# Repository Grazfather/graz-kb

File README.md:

# Graziano's keyboard

[ZMK configuration and keymap](https://github.com/Grazfather/zmk-config-grazkb)

* 58 key ergonomic wires keyboard.
* Full number row and alphabet (bare minimum for me)
* Low-profile choc switches
* 5 keys in the thumb cluster/row
* Designed using [Ergogen](https://github.com/ergogen/ergogen) and KiCad.
* ZMK Used for firmware.

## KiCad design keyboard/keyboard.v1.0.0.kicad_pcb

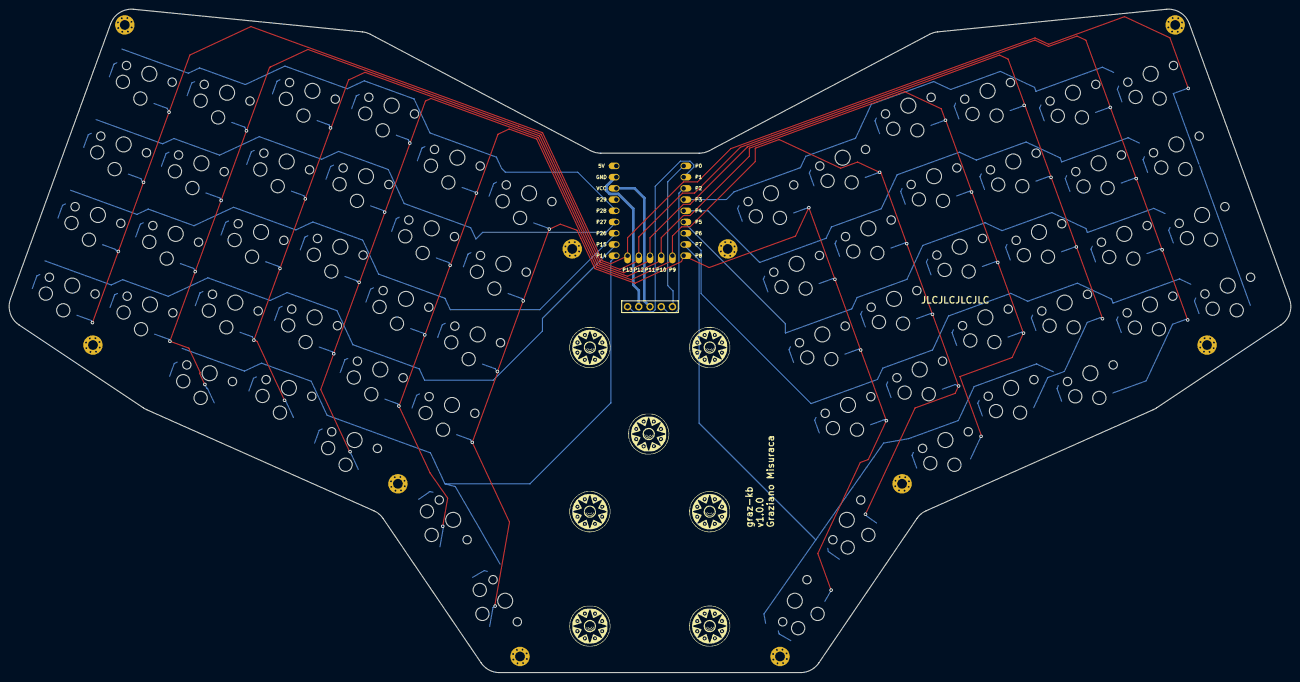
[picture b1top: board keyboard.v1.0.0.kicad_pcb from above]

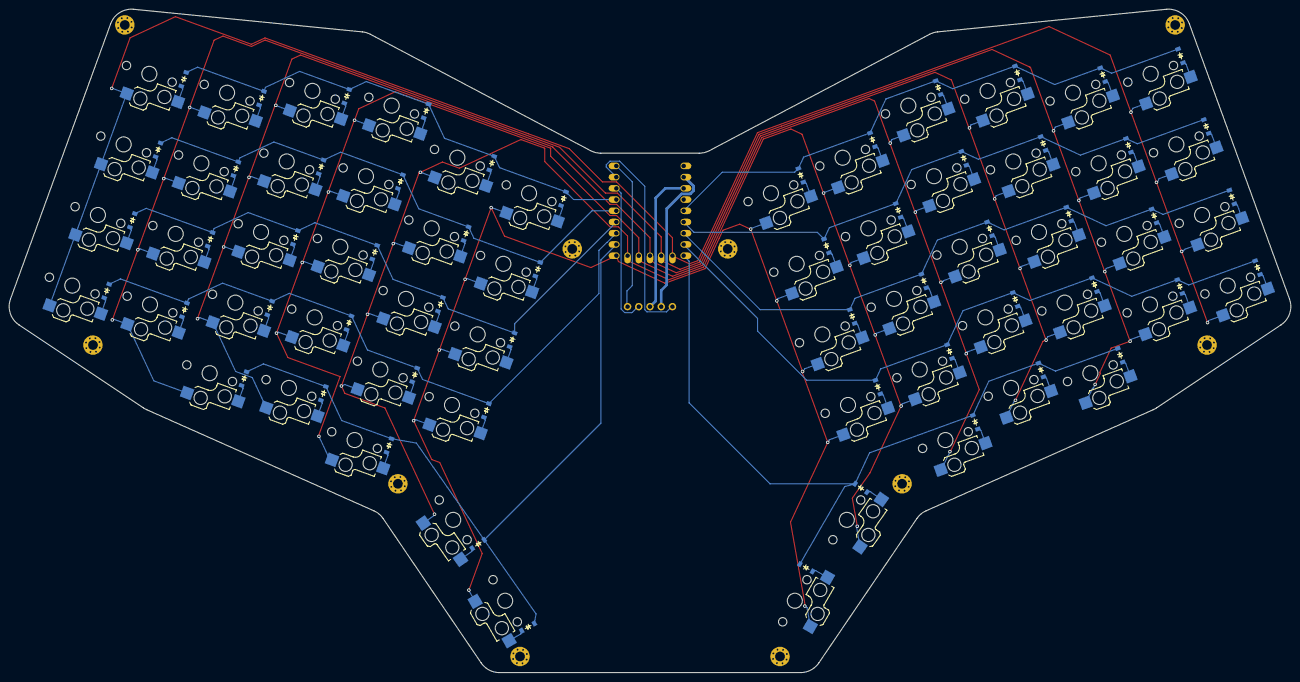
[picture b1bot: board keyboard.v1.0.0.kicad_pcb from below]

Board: 2 copper layers, 290.1 x 150.1 mm, 128 parts (116 on the bottom side), 79 nets.

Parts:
D1, D2, D3, D4, D5, D6, D7, D8, D9, D10, D11, D12, D13, D14, D15, D16, D17, D18, D19, D20, D21, D22, D23, D24, D25, D26, D27, D28, D29, D30, D31, D32, D33, D34, D35, D36, D37, D38, D39, D40, D41, D42, D43, D44, D45, D46, D47, D48, D49, D50, D51, D52, D53, D54, D55, D56, D57, D58: diode_tht_sod123
DISP1: nice_view
MCU1: Waveshare RP2040 Zero
S1, S2, S3, S4, S5, S6, S7, S8, S9, S10, S11, S12, S13, S14, S15, S16, S17, S18, S19, S20, S21, S22, S23, S24, S25, S26, S27, S28, S29, S30, S31, S32, S33, S34, S35, S36, S37, S38, S39, S40, S41, S42, S43, S44, S45, S46, S47, S48, S49, S50, S51, S52, S53, S54, S55, S56, S57, S58: switch_choc_v1_v2
_1, _2, _3, _3#2, _3#3, _4, _5, _6, _7, _8: MountingHole_2.2mm_M2_Pad_Via

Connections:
GND: DISP1.2, MCU1.22
OLED_MOSI: DISP1.5, MCU1.1
OLED_SCK: DISP1.4, MCU1.3
OLED_SS: DISP1.1, MCU1.2
VCC: DISP1.3, MCU1.21
col_index: MCU1.10, S20.1, S21.1, S22.1, S23.1, S28.1, S49.1, S50.1, S51.1, S52.1, S57.1
col_inner: MCU1.9, S24.1, S25.1, S26.1, S27.1, S29.1, S53.1, S54.1, S55.1, S56.1, S58.1
col_middle: MCU1.11, S15.1, S16.1, S17.1, S18.1, S19.1, S44.1, S45.1, S46.1, S47.1, S48.1
col_outer: MCU1.14, S1.1, S2.1, S3.1, S4.1, S30.1, S31.1, S32.1, S33.1
col_pinky: MCU1.13, S5.1, S6.1, S7.1, S8.1, S9.1, S34.1, S35.1, S36.1, S37.1, S38.1
col_ring: MCU1.12, S10.1, S11.1, S12.1, S13.1, S14.1, S39.1, S40.1, S41.1, S42.1, S43.1
far_thumb: D29.2, S29.2
home_thumb: D28.2, S28.2
index_bottom: D20.2, S20.2
index_home: D21.2, S21.2
index_mod: D19.2, S19.2
index_num: D23.2, S23.2
index_top: D22.2, S22.2
inner_bottom: D24.2, S24.2
inner_home: D25.2, S25.2
inner_num: D27.2, S27.2
inner_top: D26.2, S26.2
middle_bottom: D15.2, S15.2
middle_home: D16.2, S16.2
middle_mod: D14.2, S14.2
middle_num: D18.2, S18.2
middle_top: D17.2, S17.2
mirror_far_thumb: D58.2, S58.2
mirror_home_thumb: D57.2, S57.2
mirror_index_bottom: D49.2, S49.2
mirror_index_home: D50.2, S50.2
mirror_index_mod: D48.2, S48.2
mirror_index_num: D52.2, S52.2
mirror_index_top: D51.2, S51.2
mirror_inner_bottom: D53.2, S53.2
mirror_inner_home: D54.2, S54.2
mirror_inner_num: D56.2, S56.2
mirror_inner_top: D55.2, S55.2
mirror_middle_bottom: D44.2, S44.2
mirror_middle_home: D45.2, S45.2
mirror_middle_mod: D43.2, S43.2
mirror_middle_num: D47.2, S47.2
mirror_middle_top: D46.2, S46.2
mirror_outer_bottom: D30.2, S30.2
mirror_outer_home: D31.2, S31.2
mirror_outer_num: D33.2, S33.2
mirror_outer_top: D32.2, S32.2
mirror_pinky_bottom: D34.2, S34.2
mirror_pinky_home: D35.2, S35.2
mirror_pinky_num: D37.2, S37.2
mirror_pinky_top: D36.2, S36.2
mirror_ring_bottom: D39.2, S39.2
mirror_ring_home: D40.2, S40.2
mirror_ring_mod: D38.2, S38.2
mirror_ring_num: D42.2, S42.2
mirror_ring_top: D41.2, S41.2
mirror_row_bottom: D30.1, D34.1, D39.1, D44.1, D49.1, D53.1, MCU1.7
mirror_row_home: D31.1, D35.1, D40.1, D45.1, D50.1, D54.1, MCU1.6
mirror_row_mod: D38.1, D43.1, D48.1, D57.1, D58.1, MCU1.8
mirror_row_num: D33.1, D37.1, D42.1, D47.1, D52.1, D56.1, MCU1.4
mirror_row_top: D32.1, D36.1, D41.1, D46.1, D51.1, D55.1, MCU1.5
outer_bottom: D1.2, S1.2
outer_home: D2.2, S2.2
outer_num: D4.2, S4.2
outer_top: D3.2, S3.2
pinky_bottom: D5.2, S5.2
pinky_home: D6.2, S6.2
pinky_num: D8.2, S8.2
pinky_top: D7.2, S7.2
ring_bottom: D10.2, S10.2
ring_home: D11.2, S11.2
ring_mod: D9.2, S9.2
ring_num: D13.2, S13.2
ring_top: D12.2, S12.2
row_bottom: D1.1, D5.1, D10.1, D15.1, D20.1, D24.1, MCU1.16
row_home: D2.1, D6.1, D11.1, D16.1, D21.1, D25.1, MCU1.17
row_mod: D9.1, D14.1, D19.1, D28.1, D29.1, MCU1.15
row_num: D4.1, D8.1, D13.1, D18.1, D23.1, D27.1, MCU1.19
row_top: D3.1, D7.1, D12.1, D17.1, D22.1, D26.1, MCU1.18

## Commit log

2024-03-02 Add reqs
2024-03-02 layout: Move mods a row in, splay thumb more
2024-03-03 Add PCB tips resource
2024-03-03 Adjust thumb fan position
2024-03-07 Shift mod row in
2024-03-07 Add stuff for pcb
2024-03-08 Add extra key and reorg
2024-03-08 Reorg, adjust rotation, and bring sides closer
2024-03-08 Add exports
2024-03-08 Add flatfootfox tutorial series resource
2024-03-13 Create extra keyboard with less mods, create PCBs
2024-03-13 Add notes about parts
2024-03-13 Rename ergogen yaml to config.yaml
2024-03-13 Add mounting holes
2024-03-14 Adjust outline slightly
2024-03-14 Get column nets working with thumb
2024-03-15 Get mirrored half column nets on their own
2024-03-20 Fix index finger stagger
2024-03-20 Switch to 10 row 6 column and assign pins + oled
2024-03-20 Add more resources
2024-03-24 Add more parts in readme
2024-03-24 Move nice view pins to params
2024-03-25 Add ceoloide's ergogen-footprints as a submodule
2024-03-26 Fix row and column nets on thumb cluster
2024-03-26 wip: Add per-key LEDs
2024-03-27 Adjust mounting holes so they don't interfere with any pads or switches
2024-03-31 Resist mirroring for diodes
2024-03-31 Move col/row nets to closer side of MCU
2024-04-01 update ceoloide's footprints
2024-04-01 Add models to footprints
2024-04-01 Move mounting holes so they aren't under any keys
2024-05-13 WIP: Per-key LEDs
2024-05-13 Move mounting hole defs into points¬
2024-05-13 Fix positioning of OLED display
2024-05-13 Add more mounting holes and move some
2024-05-13 Add LED model
2024-05-13 Cleanup ergogen config
2024-05-13 Fix VCC nets
2024-05-13 Adjust some column stagger
2024-06-09 BUG FIX: Put OLED MOSI on actual MOSI-cap pin
2024-06-09 Version v1.1.0
2024-09-30 Cleanup and reposition
2024-09-30 Add my waveshare zero footprint
2024-09-30 Update ceoloide footprints
2024-09-30 Set orientation for rp2040
2024-09-30 Add v1.0.0 pcb file
2024-09-30 Add v1.0.0 gerber files
2024-09-30 git ignore node_modules
2024-09-30 Include silkscreen for nice_view
2024-09-30 wip: per key leds
2025-05-09 Add image
2025-05-09 Add link to zmk config repo
2025-05-09 Remove old notes and add specs
